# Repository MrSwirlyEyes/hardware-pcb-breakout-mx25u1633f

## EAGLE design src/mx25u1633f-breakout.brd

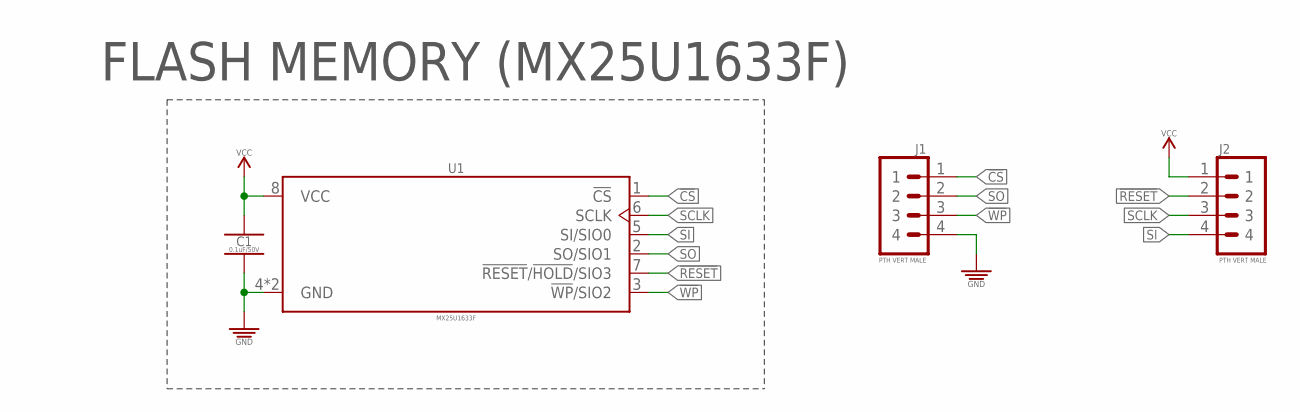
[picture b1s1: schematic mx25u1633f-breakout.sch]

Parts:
C1: 0.1uF/50V; CAPC1005X55_SMD-0402
J1, J2: PTH VERT MALE; HDRV4W64P254_1X4_1016X254X838B
U1: MX25U1633F; SON50P300X200X55-9T20X160N

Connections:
!CS!: J1.1, U1.1 (!CS)
!RESET!: J2.2, U1.7 (!RESET!/!HOLD!/SIO3)
!WP!: J1.3, U1.3 (!WP!/SIO2)
GND: C1.2, J1.4, U1.4 (GND), U1.EP (GND)
SCLK: J2.3, U1.6 (SCLK)
SI: J2.4, U1.5 (SI/SIO0)
SO: J1.2, U1.2 (SO/SIO1)
VCC: C1.1, J2.1, U1.8 (VCC)

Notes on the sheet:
FLASH MEMORY (MX25U1633F)

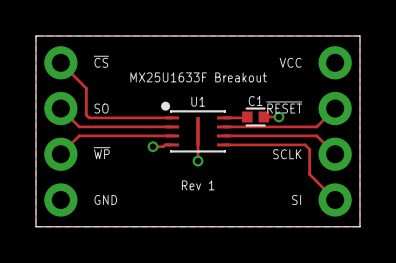
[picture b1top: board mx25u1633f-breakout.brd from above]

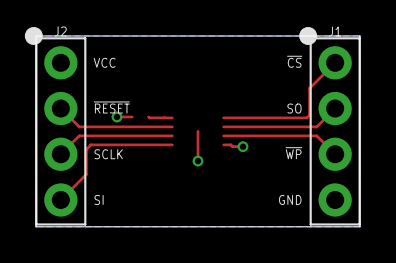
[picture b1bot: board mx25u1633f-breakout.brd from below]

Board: 2 copper layers, 18.0 x 10.6 mm, 4 parts (2 on the bottom side), 8 nets.

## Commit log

2021-01-12 [Rev 1] - Initialize repo.
2021-08-11 Update CAM files.
